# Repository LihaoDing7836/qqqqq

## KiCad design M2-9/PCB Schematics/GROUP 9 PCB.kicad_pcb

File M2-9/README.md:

# structure
├── M2-9    #the code folder
├── README.md the # readme file

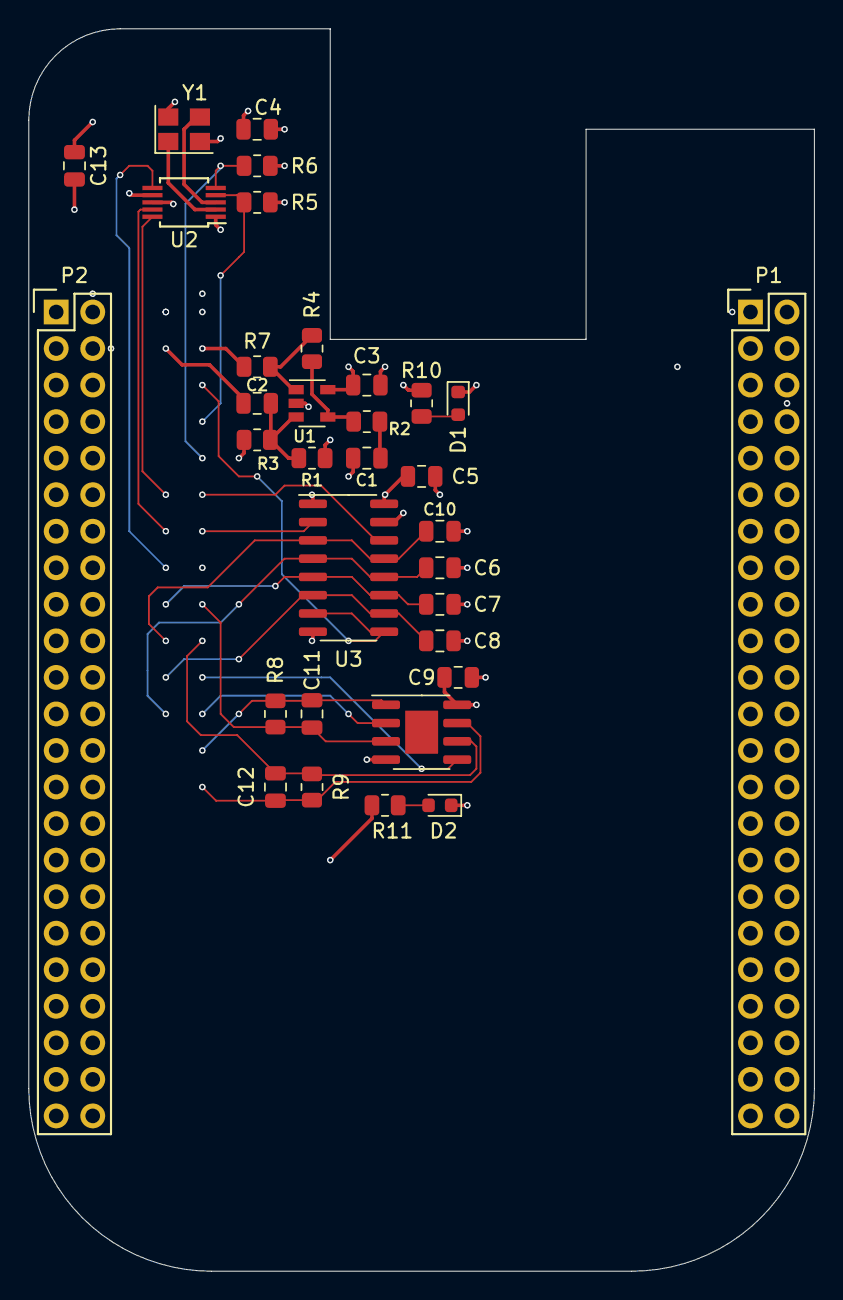
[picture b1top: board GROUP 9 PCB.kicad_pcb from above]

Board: 4 copper layers, 54.6 x 86.4 mm, 33 parts (0 on the bottom side), 23 nets.

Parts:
C1, C3, C4, C5, C6, C7, C8, C9, C10: 0.1uF; C_0805_2012Metric
C2: 0.01uF; C_0805_2012Metric
C11, C12: 3300pF; C_0805_2012Metric
C13: 10uF; C_0805_2012Metric
D1: LED yellow; D_0603_1608Metric
D2: LED blue; D_0603_1608Metric
P1, P2: BeagleBone_Black_Header; Socket_BeagleBone_Black
R1, R3: 470; R_0805_2012Metric
R2: 47; R_0805_2012Metric
R4: 220; R_0805_2012Metric
R5, R6: 4.7k; R_0805_2012Metric
R7: 100; R_0805_2012Metric
R8, R9: 10K; R_0805_2012Metric
R10: 62; R_0805_2012Metric
R11: 200; R_0805_2012Metric
U1: THS4304; SOT-23-5
U2: Si5351A-B-GT; MSOP-10_3x3mm_P0.5mm
U3: TS3A5017; SOIC-16_3.9x9.9mm_P1.27mm
U4: TL972; SOIC-8-1EP_3.9x4.9mm_P1.27mm_EP2.29x3mm
Y1: Crystal; Crystal_SMD_TXC_7M-4Pin_3.2x2.5mm

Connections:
+3V3: C3.2, C4.1, C5.1, C9.1, C13.1, P2.3, P2.4, R3.2, R5.2, R6.2, R10.1, U1.5, U2.1, U2.7, U3.16, U4.8
+5V: P2.5, P2.6
GND: C1.1, C3.1, C4.2, C5.2, C6.2, C7.2, C8.2, C9.2, C10.2, C13.2, D1.1, D2.1, P1.1, P1.2, P2.1, P2.2, P2.43, P2.44, P2.45, P2.46, R1.1, U1.2, U2.8, U3.1, U3.8, U3.15, U4.4, Y1.2, Y1.4
I2C_SCL: R5.1, U2.4
I2C_SDA: R6.1, U2.5
I+: C11.2, R8.2, U4.3
I-: C12.2, R9.2, U4.6
Iout: C11.1, R8.1, U4.1
MIXI+: C7.1, U3.5, U3.11
MIXI-: C10.1, U3.3, U3.13
MIXIN: U3.7, U3.9
MIXQ+: C8.1, U3.6, U3.10
MIXQ-: C6.1, U3.4, U3.12
unnamed: C1.2, R2.2
unnamed: C2.2, R1.2, R3.1, U1.3
unnamed: D1.2, R10.2
unnamed: D2.2, R11.2
unnamed: R2.1, R4.2, U1.4
unnamed: R4.1, R7.2, U1.1
unnamed: U2.2, Y1.1
unnamed: U2.3, Y1.3
Qout: C12.1, R9.1, U4.7
SYS_5V: P2.7, P2.8
